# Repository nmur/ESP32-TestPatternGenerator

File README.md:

# ESP32-TestPatternGenerator

This is a simple test pattern generator that runs on the ESP32 microcontroller and utilises the [ESP32CompositeColorVideo](https://github.com/marciot/ESP32CompositeColorVideo) library to output composite video using either the PAL and NTSC video formats. 

This tool is aimed to be used as a quick and portable was of performing tests of basic functionality for CRT TVs.

Its main features are:
- **Cheap**: Approximately <$10 USD in parts
- **Accessible**: Open source. Only a few components so soldering is easy for a first timer.
- **Small**: Roughly 2x3"/45x80mm in size.
- **Fast**: Boots and changes patterns instantly.
- **Portable**: Very low power draw, works with a powerbank or rechargeable LiPo battery.
- **Versatile**: Supports NTSC and PAL, and provides multiple test patterns.

For a similar tool aimed at 15kHz RGB video, see the [RP2040-TestPatternGenerator](https://github.com/nmur/RP2040-TestPatternGenerator).
## BOM

1. LOLIN D32 board ([Official LOLIN AliExpress store](https://www.aliexpress.us/item/2251832622236364.html), [cheaper listings](https://www.aliexpress.us/item/3256806060247101.html) may be available)
	1. 2x 16 pin headers are usually included
2. 2x 6mm push buttons ([AliExpress](https://www.aliexpress.us/item/2261799870049698.html))
3. Female composite jack ([AliExpress](https://www.aliexpress.us/item/2255800475452071.html))
4. Composite video cable if you don't already have one ([AliExpress](https://www.aliexpress.us/item/3256806419160332.html))
## Building a Board

1. Download the latest [Gerber zip file](https://github.com/nmur/ESP32-TestPatternGenerator/blob/main/plots/ESP32-TestPatternGenerator.zip).
2. Upload and print the Gerber file to a PCB manufacturing website (such as JLCPCB or PCBWay).
3. Solder the components into their marked positions. 

The circuit is simple enough that a PCB isn't necessary, especially if you would just like to try the tool out first with a breadboard or protoboard. You can even splice a composite video cable and wire the ends directly to the ESP32 board pins, and you can omit the buttons if you don't need every pattern (the tool remembers the last video format).

The schematic is available [here](https://raw.githubusercontent.com/nmur/ESP32-TestPatternGenerator/refs/heads/main/img/schematic.png).
## Uploading the Firmware

Navigate to the [Installation page](https://nmur.github.io/ESP32-TestPatternGenerator-WebInstaller/) to connect to your device and flash the firmware from your browser directly. You'll need to install [CH340 drivers](https://www.wch-ic.com/downloads/CH341SER_ZIP.html) in order

## How to Use

Power the device using USB or and LiPo battery, and connect the composite cable to you CRT TV. Cycle through test patterns with the `Pattern` button, and toggle between video formats with the `PAL/NTSC` button. 

The device will remember the last video format so you don't need to toggle it to your region every time it boots.
## Limitations

Currently the available colours are limited to a palette of 256 colours. As such, noticeable colour banding will be present.

## Compiling

1. Clone the repository
2. Open the `ESP32-TestPatternGenerator.ino` file with the Arduino IDE
3. Install version 1.0.6 of the ESP32 board manager
4. Connect your device via USB
5. Build and upload the program

## Acknowledgements

- [bitluni](https://www.youtube.com/@bitluni) for his original [ESP32CompositeVideo](https://github.com/bitluni/ESP32CompositeVideo) project
- [marciot](https://github.com/marciot) for his [ESP32CompositeColorVideo](https://github.com/marciot/ESP32CompositeColorVideo) library forked from the original project above
- [rossumur](https://github.com/rossumur) for his work on the [ESP_8_BIT](https://github.com/rossumur/esp_8_bit) project
- [Artemio Urbina](https://github.com/ArtemioUrbina) for his test patterns

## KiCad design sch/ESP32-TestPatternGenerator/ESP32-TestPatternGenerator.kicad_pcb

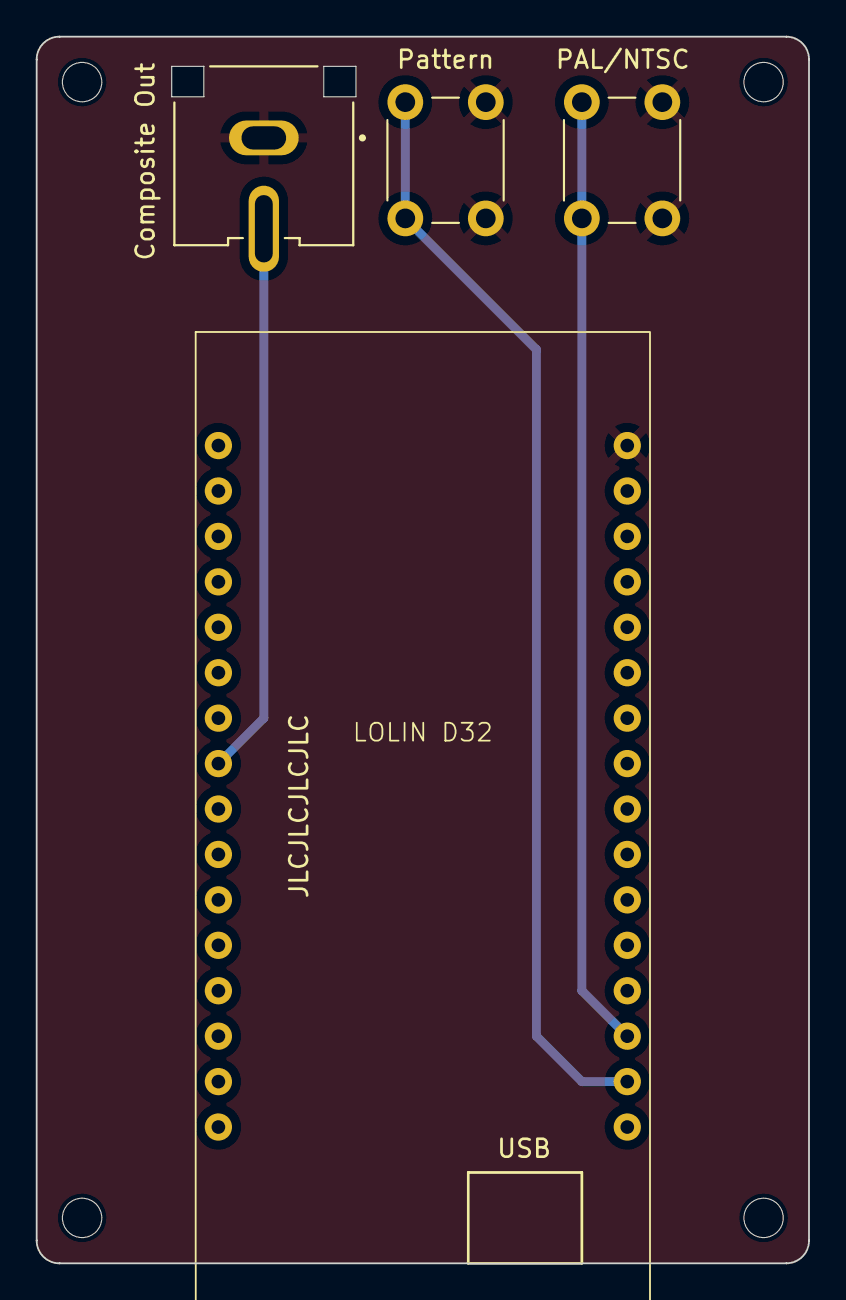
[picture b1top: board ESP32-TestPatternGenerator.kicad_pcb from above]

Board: 2 copper layers, 43.2 x 68.6 mm, 4 parts (0 on the bottom side), 3 nets.

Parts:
Composite Out: Composite Out; CUI_RCJ-044
LOLIN D32: LOLIN_D32
PAL/NTSC: Format; SW_PUSH_6mm_H4.3mm
Pattern: Pattern; SW_PUSH_6mm_H4.3mm

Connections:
unnamed: Composite Out.1 (In), LOLIN D32.8 (IO25)
unnamed: LOLIN D32.30 (IO2), PAL/NTSC.1
unnamed: LOLIN D32.31 (IO15), Pattern.1

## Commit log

2024-10-12 created skeleton arduino project
2024-10-12 completed barebones colorbar pattern code
2024-10-12 added minor build note to readme
2024-10-14 initial attempt at switching regions, toggles between PAL/NTSC every 2 secs
2024-10-14 made the video format toggle on button press
2024-10-14 removed unnecessary debounce code (as we restart the device anyway), cleanup/refactor
2024-10-15 add image conversion script
2024-10-15 added three new basic patterns
2024-10-15 loop through all the patterns on a timer
2024-10-16 added button handler to cycle through test patterns (without debounce)
2024-10-16 implemented debounce
2024-10-16 added schematic including custom symbol library for LOLIN32
2024-10-16 first pass of the PCB
2024-10-16 finalised PCB
2024-10-16 added v1.0 gerber
2024-10-16 minor changes
2024-10-16 Rename plots.zip to ESP32-TestPatternGenerator.zip
2024-10-16 Create test
2024-10-16 Rename image.png to shematic.png
2024-10-16 Rename shematic.png to schematic.png
2024-10-30 increased composite pin hole clearance
2024-10-30 added JLCPCB order number marker and USB positioning aid labels on silkscreen
2024-10-30 exported v1.1 gerber
2025-07-19 wip commit
2025-07-19 remove V1 files
2025-07-19 add first pass of V2 on M5StickC (display example)
2025-07-19 battery level display
